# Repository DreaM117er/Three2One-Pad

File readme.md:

# Three2One Pad

## Description

### What is 321 Pad?

Three2One Pad is a small keyboard pad for persional function keys. It supported maxium 12 keyboard keys or 8 keyboard keys + 4 rotray encoder, MX switches hotswap, and used RP2040 mini series micro controller (ex. supermini/zero... etc) to drive.

This is a simple repostiory, it would be opensource all files on here, check files inside floder.

### Layout and Keymap

## PCB & 3D module

|||
|---|---|
|||

## Building Guide

### Material

|Item|Amount|Note|
|---|---|---|
|PCB|1|-|
|MCU|1|RP2040 `SuperMini`/`Zero`|
|Cases|1|`Acrylic` or `3DP`|
|Hotswap Socket|8-12|`MX` version|
|Diodes `1N4148`|12|`SOD-123` or `DO-35` version|
|`M2x5mm` Screw|12|for `Arcylic case`|
|`M2x6mm` Spacer|6|for `Arcylic case`|
|Rotray Encoder `EC-11`|0-4|`Personal Option`|
|Rubber feets|4|`ø8mm`, `H1mm`|

### Guide.1: PCB part

- Prepare hotswap sockets and solder gun, you need to install them first.

- Then install diodes to PCB.

- Cut off useless diode feets after solder 1N4148 diodes.

- If you finished solder diodes, next way is install MCU.

- Install pin header to PCB then put MCU on top of headers.

- Rotray Encoders are persional option. If you want to install them, please decide to install 0-4 EC-11(s) on the PCB.

- Last step flash firmware and test how's the pad working.

> **Note**
>
> RP2040 SuperMini/Zero have same `bootloader` way, you need to keep pushing switch on the MCU `before` plug USB-C cable to the PC. After that, you can see a `disk` on your device, then put `.uf2` firmware file into disk.

### Guide.2: Case part

- First install spacers on PCB and bottom case.

- Put the PCB on bottom case, then install plate and cover.

- If you finish case installed, put 4 rubber feets below the bottom case.

- Last step, put MX switches and keycaps on the pad.

- Done.

## Informations and Special Thanks

- [QMK Firmware](https://qmk.fm/).
- [VIAL](https://get.vial.today/).
- [KiCAD](https://www.kicad.org/) version `7.0.5.`
- [JLCPCB](https://jlcpcb.com/).
- [AutoDesk Fusion360](https://www.autodesk.com/products/fusion-360/free-trial).
- Taiwan [Tatung University](https://www.ttu.edu.tw/) - [Department of Mechanical and Materials Engineering](https://mme.ttu.edu.tw/)
- And my friend: [YCT](https://github.com/yct38)

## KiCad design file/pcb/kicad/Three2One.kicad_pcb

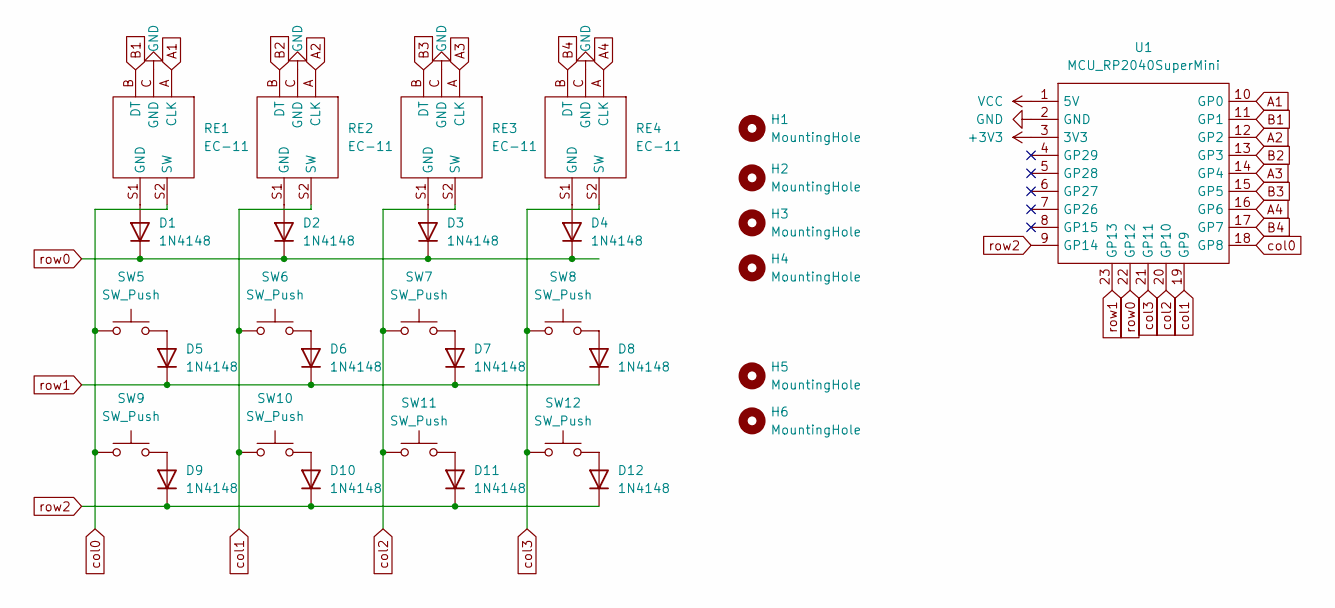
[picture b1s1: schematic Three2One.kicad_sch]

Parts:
D1, D2, D3, D4, D5, D6, D7, D8, D9, D10, D11, D12: 1N4148; D_DO-35_SOD27_P7.62mm_Horizontal
H1, H2, H3, H4: MountingHole; MountingHole_3.5mm
H5, H6: MountingHole; MountingHole_2.2mm_M2
RE1, RE2, RE3, RE4: EC-11; SW_Hotswap_Kailh_MX_Plated_1.00u_withEC-11
SW5, SW6, SW7, SW8, SW9, SW10, SW11, SW12: SW_Push; SW_Hotswap_Kailh_MX_Plated_1.00u
U1: MCU_RP2040SuperMini

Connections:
+3V3: U1.3 (3V3)
A1: RE1.A (CLK), U1.10 (GP0)
A2: RE2.A (CLK), U1.12 (GP2)
A3: RE3.A (CLK), U1.14 (GP4)
A4: RE4.A (CLK), U1.16 (GP6)
B1: RE1.B (DT), U1.11 (GP1)
B2: RE2.B (DT), U1.13 (GP3)
B3: RE3.B (DT), U1.15 (GP5)
B4: RE4.B (DT), U1.17 (GP7)
GND: RE1.C (GND), RE2.C (GND), RE3.C (GND), RE4.C (GND), U1.2 (GND)
unnamed: D1.2 (A), RE1.S1 (GND)
unnamed: D2.2 (A), RE2.S1 (GND)
unnamed: D3.2 (A), RE3.S1 (GND)
unnamed: D4.2 (A), RE4.S1 (GND)
unnamed: D5.2 (A), SW5.2
unnamed: D6.2 (A), SW6.2
unnamed: D7.2 (A), SW7.2
unnamed: D8.2 (A), SW8.2
unnamed: D9.2 (A), SW9.2
unnamed: D10.2 (A), SW10.2
unnamed: D11.2 (A), SW11.2
unnamed: D12.2 (A), SW12.2
VCC: U1.1 (5V)
col0: RE1.S2 (SW), SW5.1, SW9.1, U1.18 (GP8)
col1: RE2.S2 (SW), SW6.1, SW10.1, U1.19 (GP9)
col2: RE3.S2 (SW), SW7.1, SW11.1, U1.20 (GP10)
col3: RE4.S2 (SW), SW8.1, SW12.1, U1.21 (GP11)
row0: D1.1 (K), D2.1 (K), D3.1 (K), D4.1 (K), U1.22 (GP12)
row1: D5.1 (K), D6.1 (K), D7.1 (K), D8.1 (K), U1.23 (GP13)
row2: D9.1 (K), D10.1 (K), D11.1 (K), D12.1 (K), U1.9 (GP14)

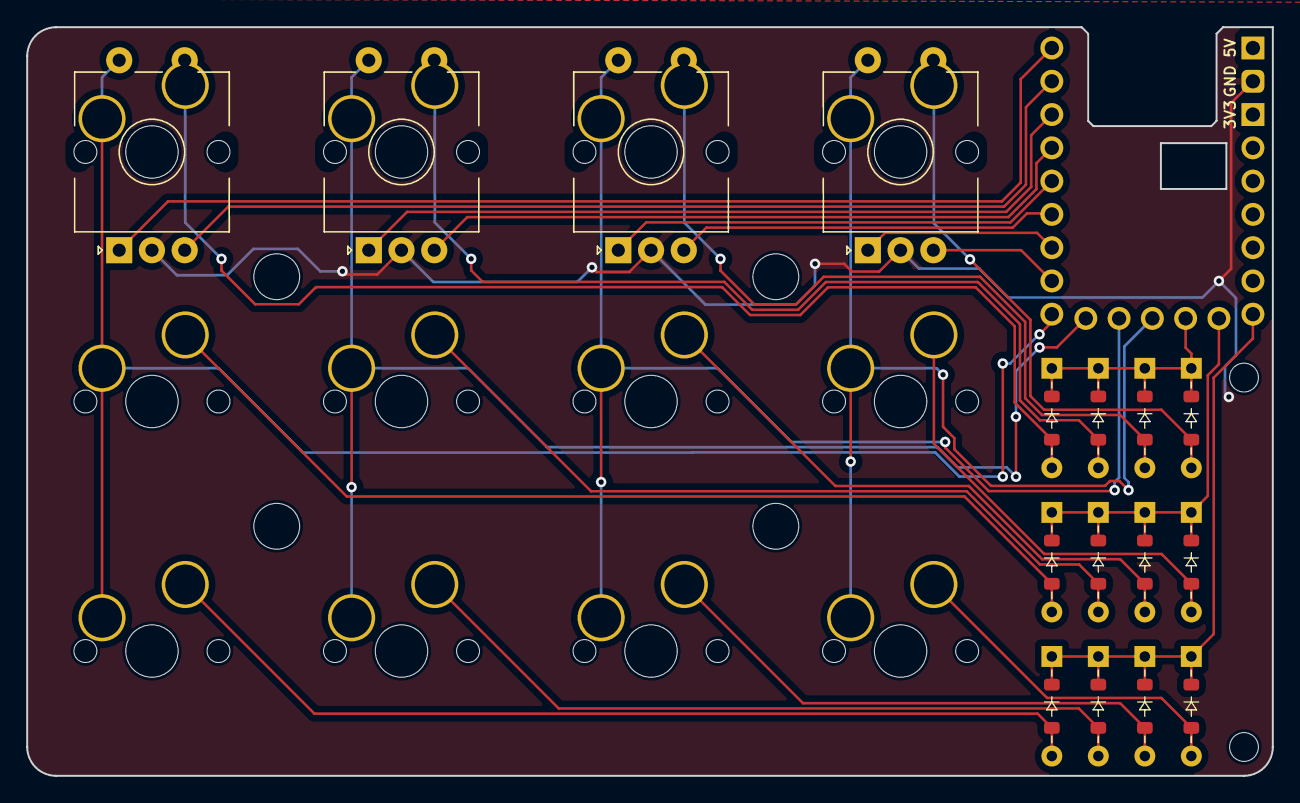
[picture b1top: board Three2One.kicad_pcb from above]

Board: 2 copper layers, 95.1 x 57.1 mm, 31 parts (1 on the bottom side), 28 nets.

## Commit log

2023-11-04 update readme.md & files
2023-11-11 update 3DP case
2023-11-15 update info pics
2023-12-02 fix arc case
2023-12-04 update building guide
2023-12-11 fix 3DP case and module
2023-12-15 fix 3DP case plate
2023-12-16 fix 3DP case
